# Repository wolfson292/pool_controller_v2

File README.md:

# pool_controller_v2
ESPHome Based Pool &amp; Spa Automation Controller

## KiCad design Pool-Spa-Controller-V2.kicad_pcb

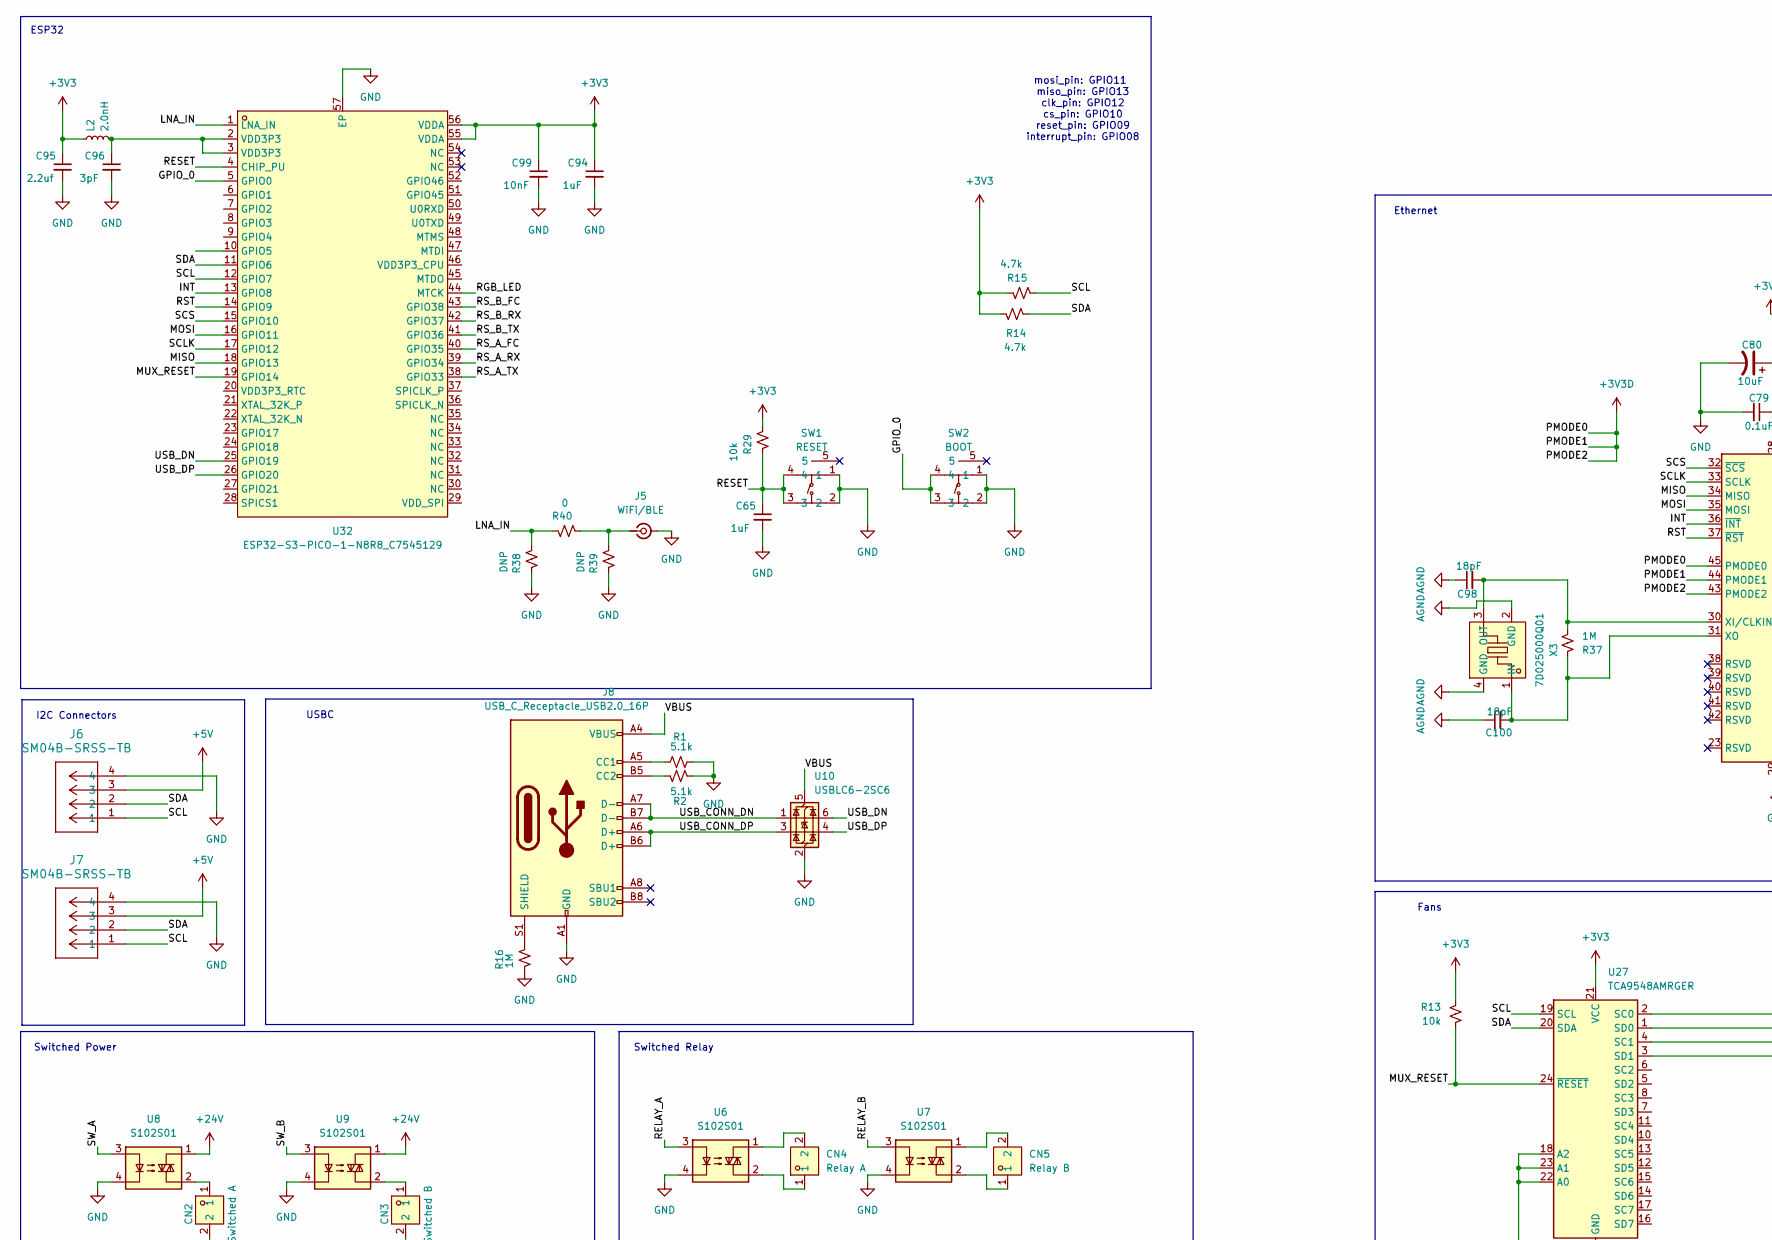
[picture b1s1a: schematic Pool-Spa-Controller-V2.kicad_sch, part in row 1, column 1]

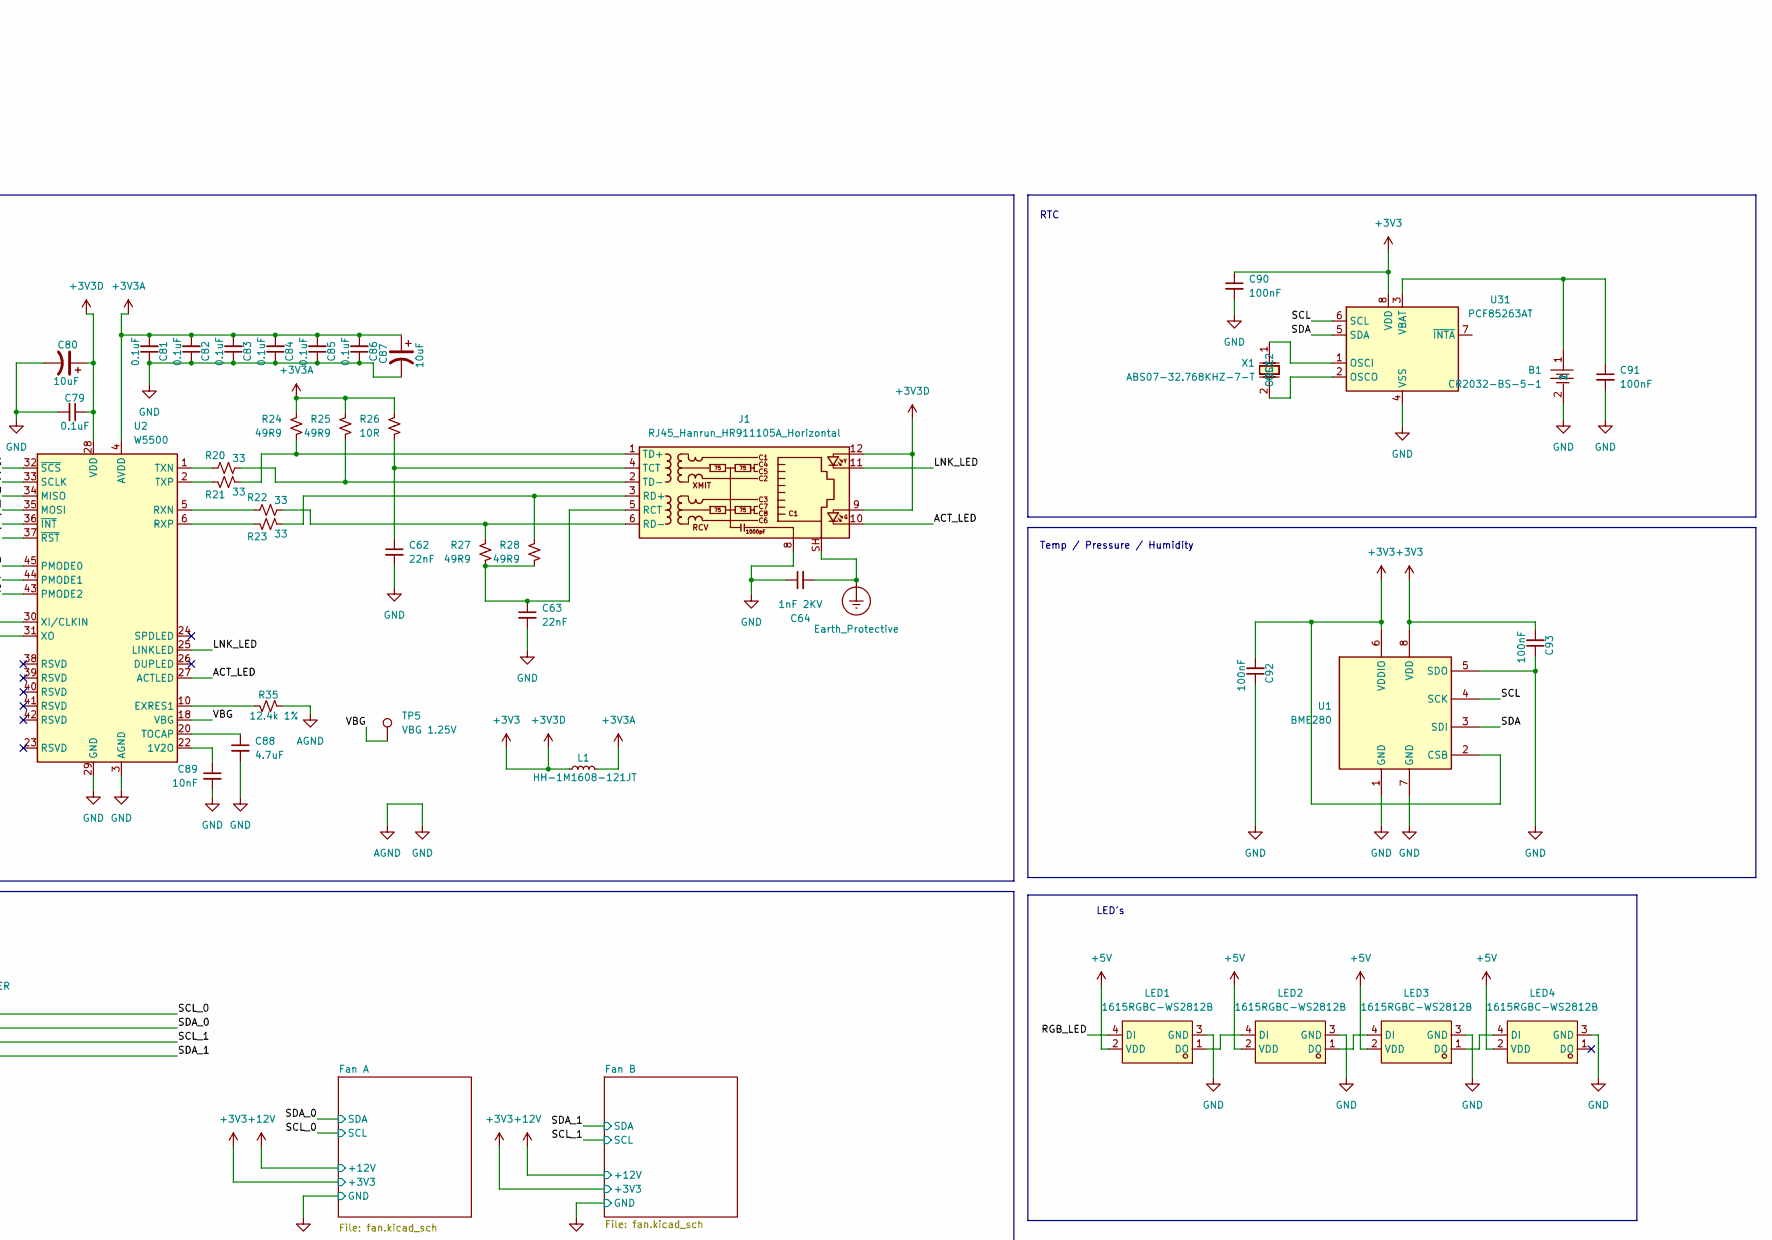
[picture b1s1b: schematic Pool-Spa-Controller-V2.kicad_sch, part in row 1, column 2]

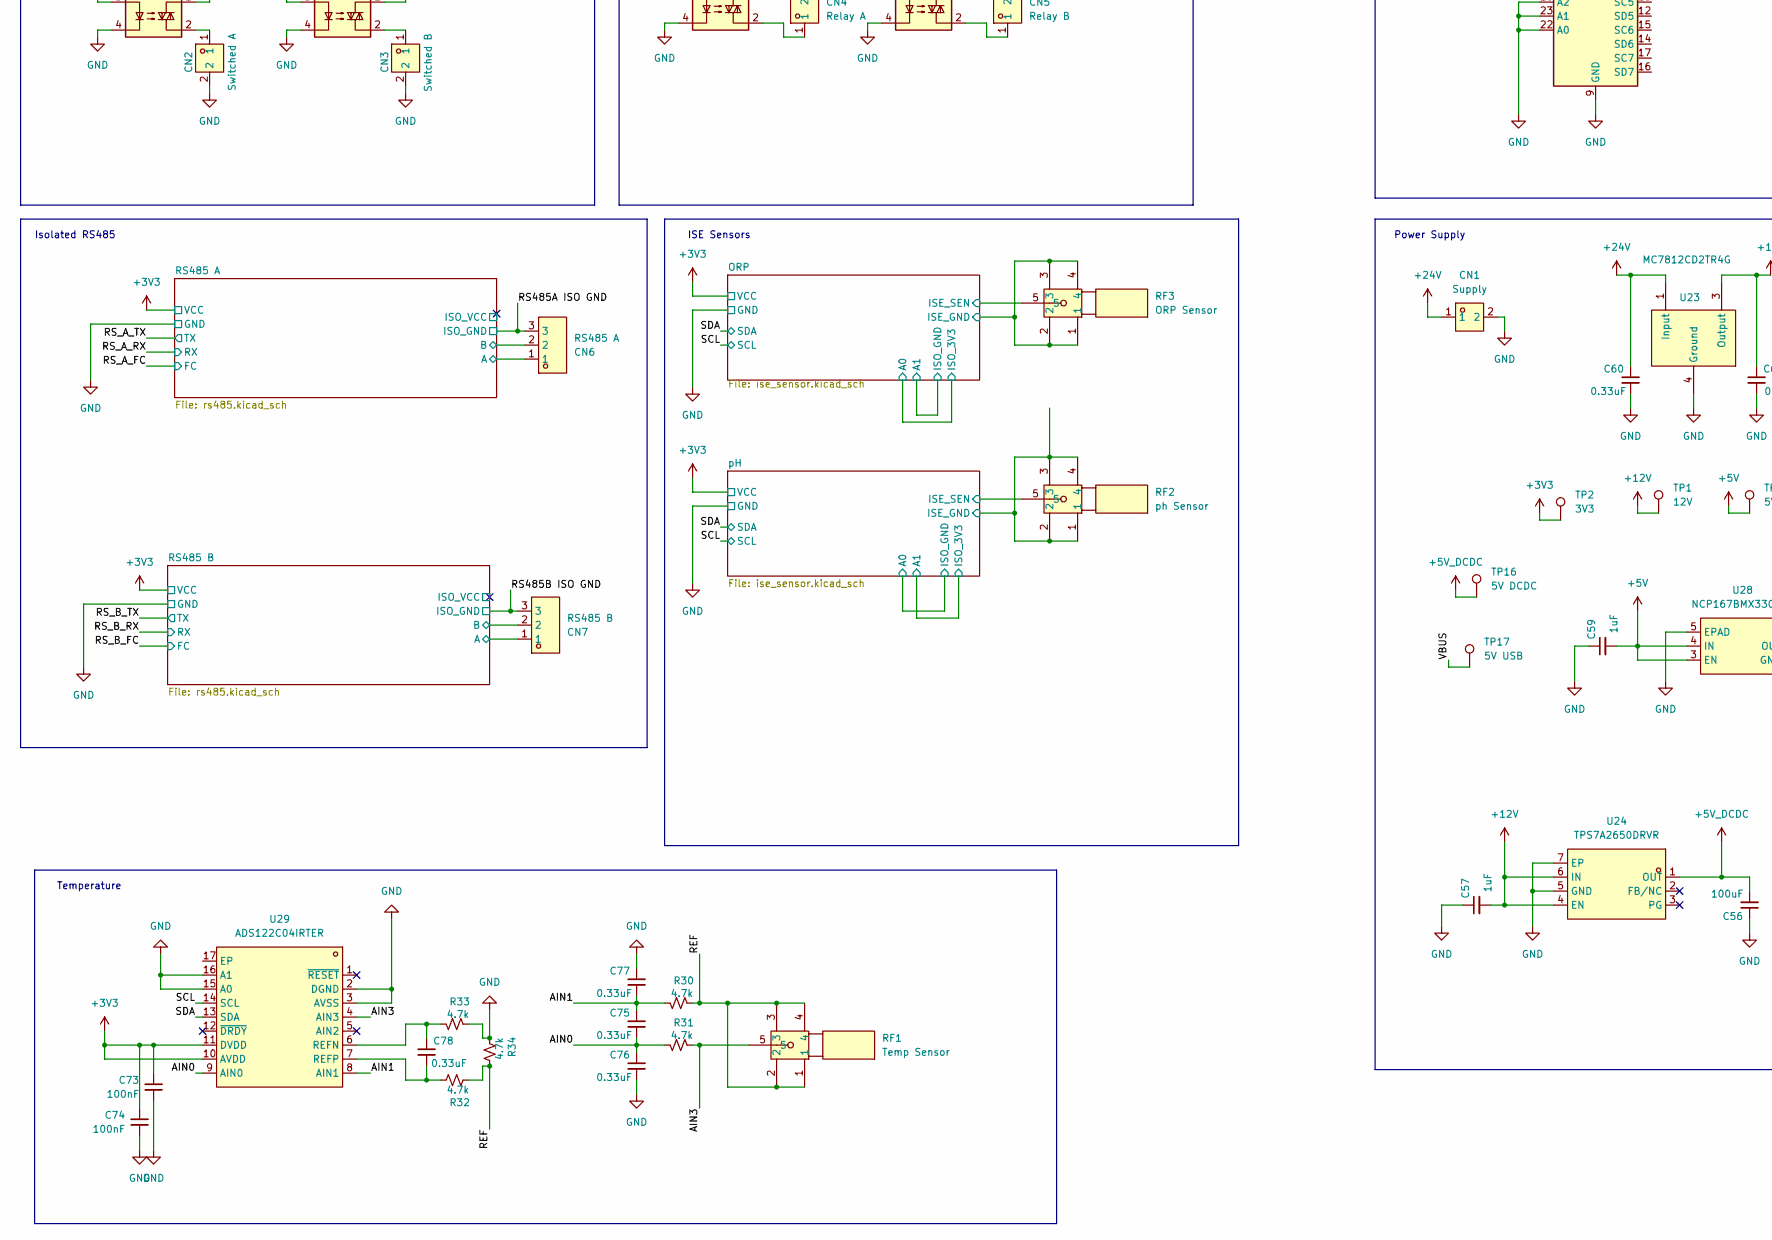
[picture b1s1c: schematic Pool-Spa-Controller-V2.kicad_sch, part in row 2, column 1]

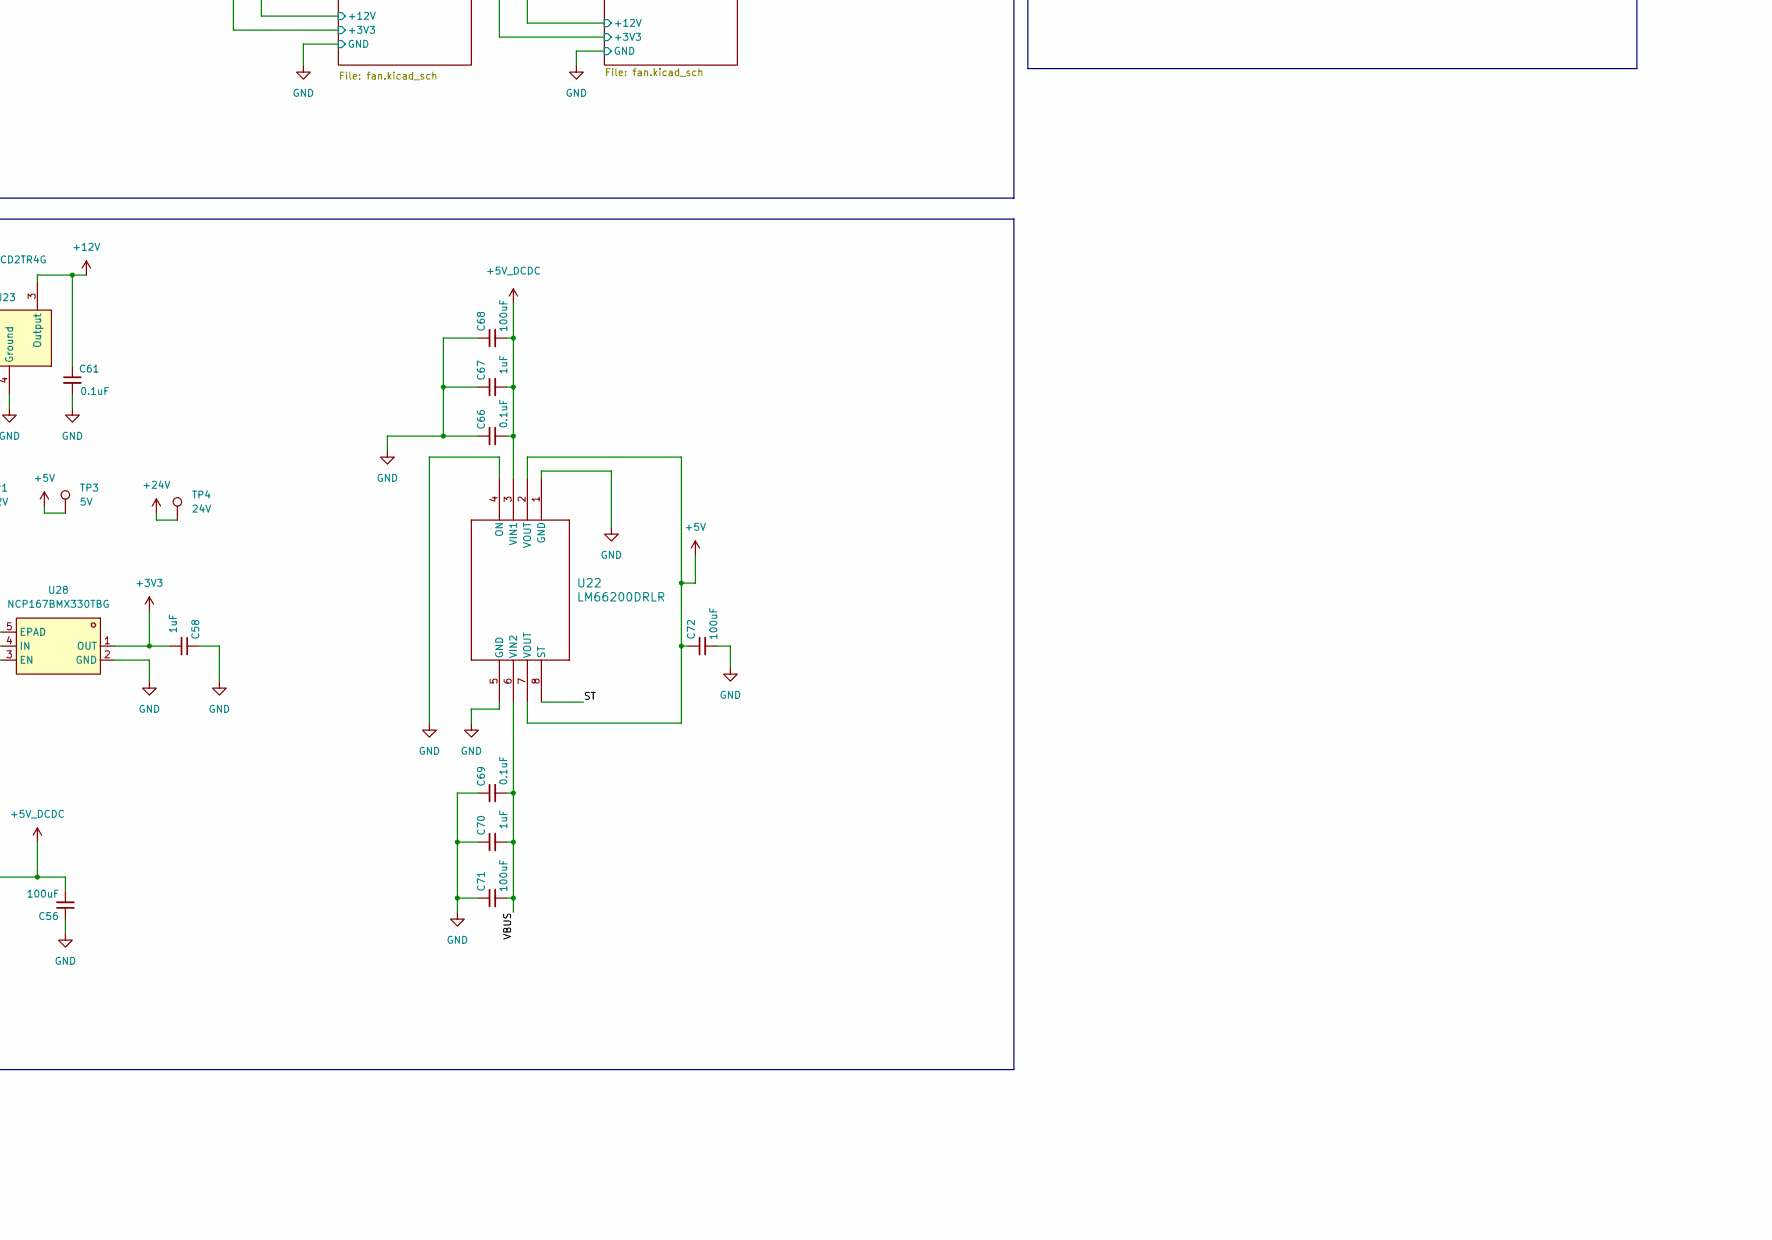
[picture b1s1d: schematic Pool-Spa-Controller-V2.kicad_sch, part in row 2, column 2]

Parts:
B1: CR2032-BS-5-1; BAT-TH_CR2032-BS-5-1; LCSC Part C70379
C56, C68, C71, C72: 100uF; C_0402_1005Metric
C57, C58, C59, C65, C67, C70, C94: 1uF; C_0402_1005Metric
C60, C75, C76, C77, C78: 0.33uF; C_0402_1005Metric
C61, C66, C69, C79, C81, C82, C83, C84, C85, C86: 0.1uF; C_0402_1005Metric
C62, C63: 22nF; C_0402_1005Metric
C64: 1nF 2KV; C_0402_1005Metric
C73, C74: 100nF; C_0402_1005Metric; MPN 100nF 0201
C80, C87: 10uF; CP_EIA-1608-08_AVX-J
C88: 4.7uF; C_0402_1005Metric
C89, C99: 10nF; C_0402_1005Metric
C90, C91, C92, C93: 100nF; C_0402_1005Metric
C95: 2.2uf; C_0402_1005Metric
C96: 3pF; C_0402_1005Metric
C98, C100: 18pF; C_0402_1005Metric
CN1: Supply; CONN-TH_2P-P2.54_1725656; LCSC Part C3029316
CN2: Switched A; CONN-TH_2P-P2.54_1725656; LCSC Part C3029316
CN3: Switched B; CONN-TH_2P-P2.54_1725656; LCSC Part C3029316
CN4: Relay A; CONN-TH_2P-P2.54_1725656; LCSC Part C3029316
CN5: Relay B; CONN-TH_2P-P2.54_1725656; LCSC Part C3029316
CN6: RS485 A; CONN-TH_3P-P2.54_1725669; LCSC Part C5288763
CN7: RS485 B; CONN-TH_3P-P2.54_1725669; LCSC Part C5288763
J1: RJ45_Hanrun_HR911105A_Horizontal
J5: WiFi/BLE; U.FL_Molex_MCRF_73412-0110_Vertical
J6, J7: SM04B-SRSS-TB; CONN_SM04B-SRSS-TB_JST
J8: USB_C_Receptacle_USB2.0_16P; USB_C_Receptacle_G-Switch_GT-USB-7010ASV
L1: HH-1M1608-121JT; L_0603_1608Metric
L2: 2.0nH; L_0402_1005Metric
LED1, LED2, LED3, LED4: 1615RGBC-WS2812B; LED-SMD_4P-L1.6-W1.5_XL-1615RGBC-WS2812B; LCSC Part C5349954
R1, R2: 5.1k; R_0402_1005Metric
R13: 10k; R_0402_1005Metric
R14, R15: 4.7k; R_0402_1005Metric; MPN 4.7k 0201
R16, R37: 1M; R_0402_1005Metric
R20, R21, R22, R23: 33; R_0402_1005Metric
R24, R25, R27, R28: 49R9; R_0402_1005Metric
R26: 10R; R_0402_1005Metric
R29: 10k; R_0402_1005Metric; MPN 4.7k 0201
R30, R31, R32, R33, R34: 4.7k; R_0402_1005Metric
R35: 12.4k 1%; R_0402_1005Metric
R38, R39: DNP; R_0402_1005Metric; MPN 4.7k 0201
R40: 0; R_0402_1005Metric; MPN 4.7k 0201
RF1: Temp Sensor; BNC-TH_DOSIN-801-0051; LCSC Part C521210
RF2: ph Sensor; BNC-TH_DOSIN-801-0051; LCSC Part C521210
RF3: ORP Sensor; BNC-TH_DOSIN-801-0051; LCSC Part C521210
SW1: RESET; SW-SMD_5P-L4.2-W2.8-P1.60-LS4.6-TR; LCSC Part C221678
SW2: BOOT; SW-SMD_5P-L4.2-W2.8-P1.60-LS4.6-TR; LCSC Part C221678
TP1: 12V; TestPoint_Pad_D1.0mm
TP2: 3V3; TestPoint_Pad_D1.0mm
TP3: 5V; TestPoint_Pad_D1.0mm
TP4: 24V; TestPoint_Pad_D1.0mm
TP5: VBG 1.25V; TestPoint_Pad_D1.0mm
TP16: 5V DCDC; TestPoint_Pad_D1.0mm
TP17: 5V USB; TestPoint_Pad_D1.0mm
U1: BME280; Bosch_LGA-8_2.5x2.5mm_P0.65mm_ClockwisePinNumbering
U2: W5500; LQFP-48_7x7mm_P0.5mm
U6, U7, U8, U9: S102S01; SIP4_Sharp-SSR_P7.62mm_Straight
U10: USBLC6-2SC6; SOT-23-6
U22: LM66200DRLR; SOT-5X3_DRL_TEX
U23: MC7812CD2TR4G; TO-263-2_L10.0-W9.1-P5.08-LS15.2-TL; LCSC Part C38744
U24: TPS7A2650DRVR; WSON-6_L2.0-W2.0-P0.65-TL-EP; LCSC Part C2866192
U27: TCA9548AMRGER; Texas_RGE0024C_VQFN-24-1EP_4x4mm_P0.5mm_EP2.1x2.1mm
U28: NCP167BMX330TBG; XDFN-4_L1.0-W1.0-P0.65-BL-EP; LCSC Part C892227
U29: ADS122C04IRTER; WQFN-16_L3.0-W3.0-P0.50-TL-EP0.8; LCSC Part C2670105
U31: PCF85263AT; SOIC-8_3.9x4.9mm_P1.27mm
U32: ESP32-S3-PICO-1-N8R8_C7545129; QFN-56_L7.0-W7.0-P0.40-TL-EP4.0; LCSC Part C7545129
X1: ABS07-32.768KHZ-7-T; OSC-SMD_L3.2-W1.5; LCSC Part C276424
X3: 7D025000Q01; CRYSTAL-SMD_4P-L2.0-W1.6-BL; LCSC Part C648942

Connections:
+3V3: C58.2, C73.1, C74.1, C79.1, C80.1, C90.1, C92.2, C93.2, C94.1, C95.1, C99.1, J1.9, J1.12, L1.1, L2.1, R13.1, R14.1, R15.2, R29.1, TP2.1, U1.2 (CSB), U1.6 (VDDIO), U1.8 (VDD), U2.28 (VDD), U2.43 (PMODE2), U2.44 (PMODE1), U2.45 (PMODE0), U27.21 (VCC), U28.1 (OUT), U29.10 (AVDD), U29.11 (DVDD), U31.8 (VDD), U32.55 (VDDA), U32.56 (VDDA); also elsewhere on the board
+3V3A: C81.2, C82.2, C83.2, C84.2, C85.2, C86.2, C87.1, L1.2, R24.1, R25.1, R26.1, U2.4 (AVDD), U2.8 (AVDD), U2.11 (AVDD), U2.15 (AVDD), U2.17 (AVDD), U2.21 (AVDD)
+5V: C59.2, C72.1, J6.3, J7.3, LED1.2 (VDD), LED2.2 (VDD), LED3.2 (VDD), LED4.2 (VDD), TP3.1, U22.2 (VOUT), U22.7 (VOUT), U28.3 (EN), U28.4 (IN)
+5V_DCDC: C56.2, C66.2, C67.2, C68.2, TP16.1, U22.3 (VIN1), U24.1 (OUT)
+12V: C57.2, C61.1, TP1.1, U23.3 (Output), U24.4 (EN), U24.6 (IN); also elsewhere on the board
+24V: C60.1, CN1.1, TP4.1, U8.1, U9.1, U23.1 (Input)
/ACT_LED: J1.10, U2.27 (ACTLED)
/AIN0: C75.2, C76.1, R31.2, U29.9 (AIN0)
/AIN1: C75.1, C77.2, R30.2, U29.8 (AIN1)
/AIN3: R31.1, RF1.5, U29.4 (AIN3)
/GPIO_0: SW2.3, SW2.4, U32.5 (GPIO0)
/INT: U2.36 (~INT), U32.13 (GPIO8)
/LNA_IN: R38.1, R40.2, U32.1 (LNA_IN)
/LNK_LED: J1.11, U2.25 (LINKLED)
/MISO: U2.34 (MISO), U32.18 (GPIO13)
/MOSI: U2.35 (MOSI), U32.16 (GPIO11)
/MUX_RESET: R13.2, U27.24 (~RESET), U32.19 (GPIO14)
/ORP/ISE_SEN: RF3.5; also elsewhere on the board
/ORP/ISO_GND: RF3.1, RF3.2, RF3.3, RF3.4; also elsewhere on the board
/REF: R30.1, R32.1, R34.2, RF1.1, RF1.2, RF1.3, RF1.4
/RELAY_A: U6.3
/RELAY_B: U7.3
/RESET: C65.1, R29.2, SW1.3, SW1.4, U32.4 (CHIP_PU)
/RGB_LED: LED1.4 (DI), U32.44 (MTCK)
/RS485 A/A: CN6.1; also elsewhere on the board
/RS485 A/B: CN6.2; also elsewhere on the board
/RS485 B/A: CN7.1; also elsewhere on the board
/RS485 B/B: CN7.2; also elsewhere on the board
/RS485A ISO GND: CN6.3; also elsewhere on the board
/RS485B ISO GND: CN7.3; also elsewhere on the board
/RST: U2.37 (~RST), U32.14 (GPIO9)
/RS_A_FC: U32.40 (GPIO35); also elsewhere on the board
/RS_A_RX: U32.39 (GPIO34); also elsewhere on the board
/RS_A_TX: U32.38 (GPIO33); also elsewhere on the board
/RS_B_FC: U32.43 (GPIO38); also elsewhere on the board
/RS_B_RX: U32.42 (GPIO37); also elsewhere on the board
/RS_B_TX: U32.41 (GPIO36); also elsewhere on the board
/SCL: J6.1, J7.1, R15.1, U1.4 (SCK), U27.19 (SCL), U29.14 (SCL), U31.6 (SCL), U32.12 (GPIO7); also elsewhere on the board
/SCLK: U2.33 (SCLK), U32.17 (GPIO12)
/SCL_0: U27.2 (SC0); also elsewhere on the board
/SCL_1: U27.4 (SC1); also elsewhere on the board
/SCS: U2.32 (~SCS), U32.15 (GPIO10)
/SDA: J6.2, J7.2, R14.2, U1.3 (SDI), U27.20 (SDA), U29.13 (SDA), U31.5 (SDA), U32.11 (GPIO6); also elsewhere on the board
/SDA_0: U27.1 (SD0); also elsewhere on the board
/SDA_1: U27.3 (SD1); also elsewhere on the board
/ST: U22.8 (ST)
/SW_A: U8.3
/SW_B: U9.3
/USB_CONN_DN: J8.A7 (D-), J8.B7 (D-), U10.1 (I/O1)
/USB_CONN_DP: J8.A6 (D+), J8.B6 (D+), U10.3 (I/O2)
/USB_DN: U10.6 (I/O1), U32.25 (GPIO19)
/USB_DP: U10.4 (I/O2), U32.26 (GPIO20)
/VBG: TP5.1, U2.18 (VBG)
/VBUS: C69.2, C70.2, C71.2, J8.A4 (VBUS), J8.A9 (VBUS), J8.B4 (VBUS), J8.B9 (VBUS), TP17.1, U10.5 (VBUS), U22.6 (VIN2)
/pH/ISE_SEN: RF2.5; also elsewhere on the board
/pH/ISO_GND: RF2.1, RF2.2, RF2.3, RF2.4; also elsewhere on the board
AGND: B1.2, C56.1, C57.1, C58.1, C59.1, C60.2, C61.2, C62.2, C63.2, C64.1, C65.2, C66.1, C67.1, C68.1, C69.1, C70.1, C71.1, C72.2, C73.2, C74.2, C76.2, C77.1, C79.2, C80.2, C81.1, C82.1, C83.1, C84.1, C85.1, C86.1, C87.2, C88.2, C89.2, C90.2, C91.2, C92.1, C93.1, C94.2, C95.2, C96.2, C98.1, C99.2, C100.1, CN1.2, CN2.2, CN3.2, J1.8, J5.2 (Ext), J6.4, J7.4, J8.A1 (GND), J8.A12 (GND), J8.B1 (GND), J8.B12 (GND), LED1.3 (GND), LED2.3 (GND), LED3.3 (GND), LED4.3 (GND), R1.2, R2.2, R16.2, R33.1, R34.1, R35.2, R38.2, R39.2, SW1.1, SW1.2, SW2.1, SW2.2, U1.1 (GND), U1.5 (SDO), U1.7 (GND), U2.3 (AGND), U2.9 (AGND), U2.14 (AGND), U2.16 (AGND), U2.19 (AGND), U2.29 (GND), U2.48 (AGND), U6.4, U7.4, U8.4, U9.4, U10.2 (GND), U22.1 (GND), U22.4 (ON), U22.5 (GND), U23.4 (Ground), U24.5 (GND), U24.7 (EP), U27.9 (GND), U27.18 (A2), U27.22 (A0), U27.23 (A1), U28.2 (GND), U28.5 (EPAD), U29.2 (DGND), U29.3 (AVSS), U29.15 (A0), U29.16 (A1), U31.4 (VSS), U32.57 (EP), X3.2 (GND), X3.4 (GND); also elsewhere on the board
Earth_Protective: C64.2, J1.SH
unnamed: C96.1, L2.2, U32.2 (VDD3P3), U32.3 (VDD3P3)
unnamed: CN2.1, U8.2
unnamed: CN3.1, U9.2
unnamed: CN4.1, U6.2
unnamed: CN4.2, U6.1
unnamed: CN5.1, U7.2
unnamed: CN5.2, U7.1
unnamed: C63.1, J1.5 (RCT), R27.2, R28.2
unnamed: J1.3 (RD+), R23.2, R28.1
unnamed: J1.6 (RD-), R22.2, R27.1
unnamed: C62.1, J1.4 (TCT), R26.2
unnamed: J1.1 (TD+), R21.2, R24.2
unnamed: J1.2 (TD-), R20.2, R25.2
unnamed: J5.1 (In), R39.1, R40.1
unnamed: J8.A5 (CC1), R1.1
unnamed: J8.B5 (CC2), R2.1
unnamed: J8.S1 (SHIELD), R16.1
unnamed: LED1.1 (DO), LED2.4 (DI)
unnamed: LED2.1 (DO), LED3.4 (DI)
unnamed: LED3.1 (DO), LED4.4 (DI)
unnamed: C89.1, U2.22 (1V2O)
unnamed: R35.1, U2.10 (EXRES1)
unnamed: R22.1, U2.5 (RXN)
unnamed: R23.1, U2.6 (RXP)
unnamed: C88.1, U2.20 (TOCAP)
unnamed: R20.1, U2.1 (TXN)
unnamed: R21.1, U2.2 (TXP)
unnamed: C98.2, R37.2, U2.30 (XI/CLKIN), X3.3 (OUT)
unnamed: C100.2, R37.1, U2.31 (XO), X3.1 (IN)
unnamed: C78.1, R33.2, U29.6 (REFN)
unnamed: C78.2, R32.2, U29.7 (REFP)
unnamed: U31.1 (OSCI), X1.1 (OSC1)
unnamed: U31.2 (OSCO), X1.2 (OSC2)
unnamed: B1.1, C91.1, U31.3 (VBAT)

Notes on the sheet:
Switched Power
Switched Relay
ISE Sensors
Temperature
mosi_pin: GPIO11 miso_pin: GPIO13 clk_pin: GPIO12 cs_pin: GPIO10 reset_pin: GPIO09 interrupt_pin: GPIO08
I2C Connectors
LED's
USBC
Ethernet
Power Supply
RTC
ESP32
Temp / Pressure / Humidity
Isolated RS485
Fans

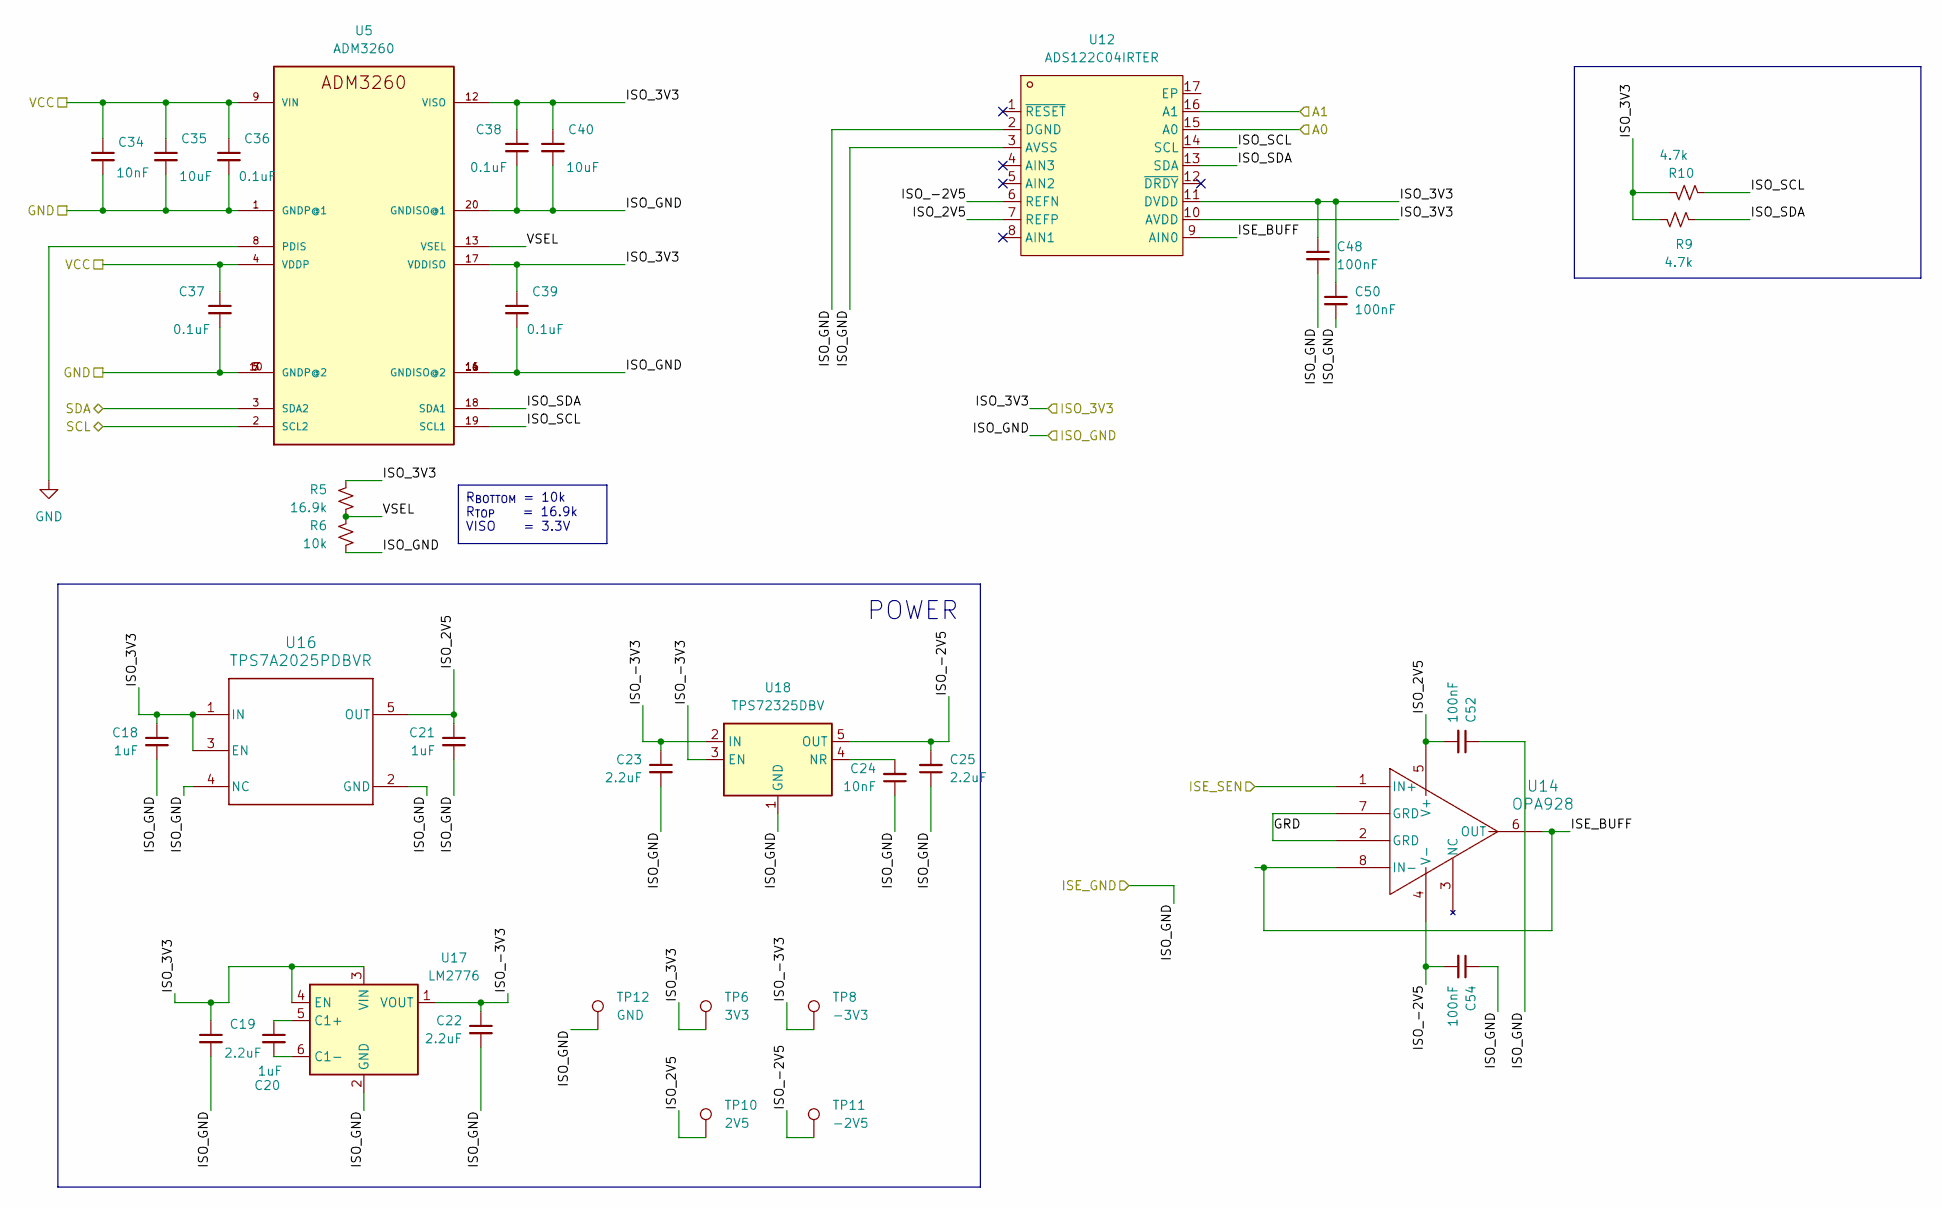
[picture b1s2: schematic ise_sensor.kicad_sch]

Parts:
C18, C20, C21: 1uF; C_0402_1005Metric; MPN 1uF 0201
C19, C22: 2.2uF; C_0402_1005Metric; MPN 1uF 0201
C23, C25: 2.2uF; C_0402_1005Metric; MPN 2.2uF 0201
C24, C34: 10nF; C_0402_1005Metric; MPN 10nF 0201
C35, C40: 10uF; C_0402_1005Metric; MPN 10uF 0201
C36, C37, C38, C39: 0.1uF; C_0402_1005Metric; MPN 0.1uF 0201
C48, C50: 100nF; C_0402_1005Metric; MPN 100nF 0201
C52, C54: 100nF; C_0402_1005Metric
R5: 16.9k; R_0402_1005Metric; MPN 30.9k 0201
R6: 10k; R_0402_1005Metric; MPN 10k 0201
R9, R10: 4.7k; R_0402_1005Metric; MPN 4.7k 0201
TP6: 3V3; TestPoint_Pad_D1.0mm
TP8: -3V3; TestPoint_Pad_D1.0mm
TP10: 2V5; TestPoint_Pad_D1.0mm
TP11: -2V5; TestPoint_Pad_D1.0mm
TP12: GND; TestPoint_Pad_D1.0mm
U5: ADM3260; ADM3260_SOP65P780X200-20N
U12: ADS122C04IRTER; WQFN-16_L3.0-W3.0-P0.50-TL-EP0.8; LCSC Part C2670105
U14: OPA928; SOIC8_D_TEX
U16: TPS7A2025PDBVR; DBV0005A-IPC_A
U17: LM2776; SOT-23-6
U18: TPS72325DBV; SOT-23-5

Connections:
+3V3: C34.1, C35.1, C36.1, C37.1, U5.4 (VDDP), U5.9 (VIN); also elsewhere on the board
/ORP/GRD: U14.2 (GRD), U14.7 (GRD)
/ORP/ISE_BUFF: U12.9 (AIN0), U14.6 (OUT), U14.8 (IN-)
/ORP/ISE_SEN: U14.1 (IN+); also elsewhere on the board
/ORP/ISO_2V5: C21.1, C52.2, TP10.1, U12.7 (REFP), U14.5 (V+), U16.5 (OUT)
/ORP/ISO_3V3: C18.1, C19.1, C38.1, C39.1, C40.1, C48.1, C50.1, R5.2, R9.1, R10.2, TP6.1, U5.12 (VISO), U5.17 (VDDISO), U12.10 (AVDD), U12.11 (DVDD), U12.15 (A0), U16.1 (IN), U16.3 (EN), U17.3 (VIN), U17.4 (EN)
/ORP/ISO_-2V5: C25.2, C54.2, TP11.1, U12.6 (REFN), U14.4 (V-), U18.5 (OUT)
/ORP/ISO_-3V3: C22.1, C23.1, TP8.1, U17.1 (VOUT), U18.2 (IN), U18.3 (EN)
/ORP/ISO_GND: C18.2, C19.2, C21.2, C22.2, C23.2, C24.1, C25.1, C38.2, C39.2, C40.2, C48.2, C50.2, C52.1, C54.1, R6.2, TP12.1, U5.11 (GNDISO@2), U5.14 (GNDISO@2), U5.16 (GNDISO@2), U5.20 (GNDISO@1), U12.2 (DGND), U12.3 (AVSS), U12.16 (A1), U16.2 (GND), U16.4 (NC), U17.2 (GND), U18.1 (GND); also elsewhere on the board
/ORP/ISO_SCL: R10.1, U5.19 (SCL1), U12.14 (SCL)
/ORP/ISO_SDA: R9.2, U5.18 (SDA1), U12.13 (SDA)
/ORP/VSEL: R5.1, R6.1, U5.13 (VSEL)
/SCL: U5.2 (SCL2); also elsewhere on the board
/SDA: U5.3 (SDA2); also elsewhere on the board
AGND: C34.2, C35.2, C36.2, C37.2, U5.1 (GNDP@1), U5.5 (GNDP@2), U5.7 (GNDP@2), U5.8 (PDIS), U5.10 (GNDP@2); also elsewhere on the board
unnamed: C20.1, U17.5 (C1+)
unnamed: C20.2, U17.6 (C1-)
unnamed: C24.2, U18.4 (NR)

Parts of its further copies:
C26, C28, C29: 1uF; C_0402_1005Metric; MPN 1uF 0201
C27, C30: 2.2uF; C_0402_1005Metric; MPN 1uF 0201
C31, C33: 2.2uF; C_0402_1005Metric; MPN 2.2uF 0201
C32, C41: 10nF; C_0402_1005Metric; MPN 10nF 0201
C42, C47: 10uF; C_0402_1005Metric; MPN 10uF 0201
C43, C44, C45, C46: 0.1uF; C_0402_1005Metric; MPN 0.1uF 0201
C49, C51: 100nF; C_0402_1005Metric; MPN 100nF 0201
C53, C55: 100nF; C_0402_1005Metric
R7: 16.9k; R_0402_1005Metric; MPN 30.9k 0201
R8: 10k; R_0402_1005Metric; MPN 10k 0201
R11, R12: 4.7k; R_0402_1005Metric; MPN 4.7k 0201
TP7: 3V3; TestPoint_Pad_D1.0mm
TP9: -3V3; TestPoint_Pad_D1.0mm
TP13: GND; TestPoint_Pad_D1.0mm
TP14: 2V5; TestPoint_Pad_D1.0mm
TP15: -2V5; TestPoint_Pad_D1.0mm
U11: ADM3260; ADM3260_SOP65P780X200-20N
U13: ADS122C04IRTER; WQFN-16_L3.0-W3.0-P0.50-TL-EP0.8; LCSC Part C2670105
U15: OPA928; SOIC8_D_TEX
U19: TPS7A2025PDBVR; DBV0005A-IPC_A
U20: LM2776; SOT-23-6
U21: TPS72325DBV; SOT-23-5

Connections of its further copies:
+3V3: C41.1, C42.1, C43.1, C44.1, U11.4 (VDDP), U11.9 (VIN); also elsewhere on the board
/SCL: U11.2 (SCL2); also elsewhere on the board
/SDA: U11.3 (SDA2); also elsewhere on the board
/pH/GRD: U15.2 (GRD), U15.7 (GRD)
/pH/ISE_BUFF: U13.9 (AIN0), U15.6 (OUT), U15.8 (IN-)
/pH/ISE_SEN: U15.1 (IN+); also elsewhere on the board
/pH/ISO_2V5: C29.1, C53.2, TP14.1, U13.7 (REFP), U15.5 (V+), U19.5 (OUT)
/pH/ISO_3V3: C26.1, C27.1, C45.1, C46.1, C47.1, C49.1, C51.1, R7.2, R11.1, R12.2, TP7.1, U11.12 (VISO), U11.17 (VDDISO), U13.10 (AVDD), U13.11 (DVDD), U13.16 (A1), U19.1 (IN), U19.3 (EN), U20.3 (VIN), U20.4 (EN)
/pH/ISO_-2V5: C33.2, C55.2, TP15.1, U13.6 (REFN), U15.4 (V-), U21.5 (OUT)
/pH/ISO_-3V3: C30.1, C31.1, TP9.1, U20.1 (VOUT), U21.2 (IN), U21.3 (EN)
/pH/ISO_GND: C26.2, C27.2, C29.2, C30.2, C31.2, C32.1, C33.1, C45.2, C46.2, C47.2, C49.2, C51.2, C53.1, C55.1, R8.2, TP13.1, U11.11 (GNDISO@2), U11.14 (GNDISO@2), U11.16 (GNDISO@2), U11.20 (GNDISO@1), U13.2 (DGND), U13.3 (AVSS), U13.15 (A0), U19.2 (GND), U19.4 (NC), U20.2 (GND), U21.1 (GND); also elsewhere on the board
/pH/ISO_SCL: R12.1, U11.19 (SCL1), U13.14 (SCL)
/pH/ISO_SDA: R11.2, U11.18 (SDA1), U13.13 (SDA)
/pH/VSEL: R7.1, R8.1, U11.13 (VSEL)
AGND: C41.2, C42.2, C43.2, C44.2, U11.1 (GNDP@1), U11.5 (GNDP@2), U11.7 (GNDP@2), U11.8 (PDIS), U11.10 (GNDP@2); also elsewhere on the board
unnamed: C28.1, U20.5 (C1+)
unnamed: C28.2, U20.6 (C1-)
unnamed: C32.2, U21.4 (NR)

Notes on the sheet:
POWER
R_{BOTTOM} = 10k R_{TOP} = 16.9k VISO = 3.3V

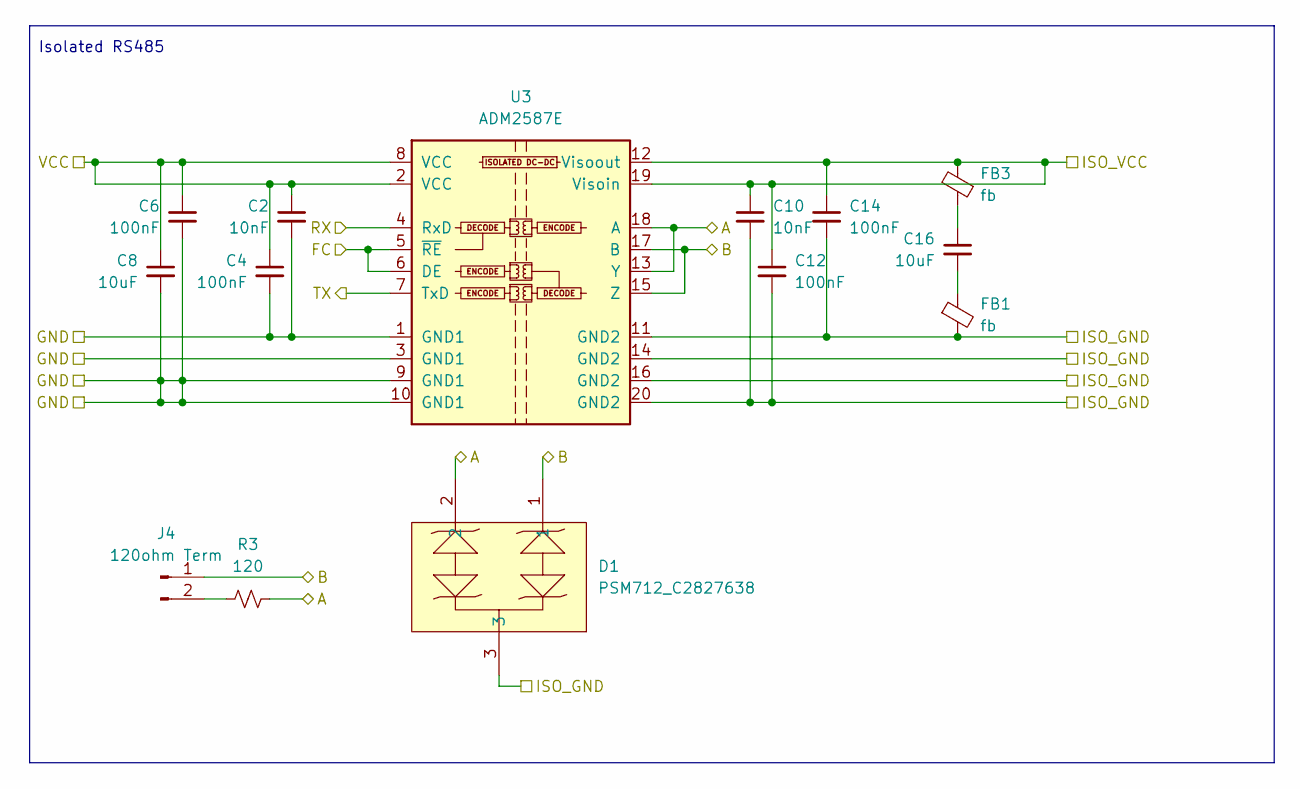
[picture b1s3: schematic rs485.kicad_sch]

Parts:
C2, C10: 10nF; C_0402_1005Metric
C4, C6, C12, C14: 100nF; C_0402_1005Metric
C8, C16: 10uF; C_0402_1005Metric
D1: PSM712_C2827638; SOT-23-3_L2.9-W1.3-P1.90-LS2.4-BL-2; LCSC Part C2827638
FB1, FB3: fb; L_0402_1005Metric
J4: 120ohm Term; PinHeader_1x02_P2.54mm_Vertical
R3: 120; R_0402_1005Metric
U3: ADM2587E; SOIC-20W_7.5x12.8mm_P1.27mm

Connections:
+3V3: C2.1, C4.1, C6.1, C8.1, U3.2 (VCC), U3.8 (VCC); also elsewhere on the board
/RS485 A/A: D1.2, R3.2, U3.13 (Y), U3.18 (A); also elsewhere on the board
/RS485 A/B: D1.1, J4.1, U3.15 (Z), U3.17 (B); also elsewhere on the board
/RS485 A/ISO_VCC: C10.1, C12.1, C14.1, FB3.2, U3.12 (Visoout), U3.19 (Visoin)
/RS485A ISO GND: C10.2, C12.2, C14.2, D1.3, FB1.2, U3.11 (GND2), U3.14 (GND2), U3.16 (GND2), U3.20 (GND2); also elsewhere on the board
/RS_A_FC: U3.5 (~RE), U3.6 (DE); also elsewhere on the board
/RS_A_RX: U3.4 (RxD); also elsewhere on the board
/RS_A_TX: U3.7 (TxD); also elsewhere on the board
AGND: C2.2, C4.2, C6.2, C8.2, U3.1 (GND1), U3.3 (GND1), U3.9 (GND1), U3.10 (GND1); also elsewhere on the board
unnamed: C16.1, FB3.1
unnamed: C16.2, FB1.1
unnamed: J4.2, R3.1

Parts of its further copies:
C3, C11: 10nF; C_0402_1005Metric
C5, C7, C13, C15: 100nF; C_0402_1005Metric
C9, C17: 10uF; C_0402_1005Metric
D2: PSM712_C2827638; SOT-23-3_L2.9-W1.3-P1.90-LS2.4-BL-2; LCSC Part C2827638
FB2, FB4: fb; L_0402_1005Metric
J9: 120ohm Term; PinHeader_1x02_P2.54mm_Vertical
R4: 120; R_0402_1005Metric
U4: ADM2587E; SOIC-20W_7.5x12.8mm_P1.27mm

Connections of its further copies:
+3V3: C3.1, C5.1, C7.1, C9.1, U4.2 (VCC), U4.8 (VCC); also elsewhere on the board
/RS485 B/A: D2.2, R4.2, U4.13 (Y), U4.18 (A); also elsewhere on the board
/RS485 B/B: D2.1, J9.1, U4.15 (Z), U4.17 (B); also elsewhere on the board
/RS485 B/ISO_VCC: C11.1, C13.1, C15.1, FB4.2, U4.12 (Visoout), U4.19 (Visoin)
/RS485B ISO GND: C11.2, C13.2, C15.2, D2.3, FB2.2, U4.11 (GND2), U4.14 (GND2), U4.16 (GND2), U4.20 (GND2); also elsewhere on the board
/RS_B_FC: U4.5 (~RE), U4.6 (DE); also elsewhere on the board
/RS_B_RX: U4.4 (RxD); also elsewhere on the board
/RS_B_TX: U4.7 (TxD); also elsewhere on the board
AGND: C3.2, C5.2, C7.2, C9.2, U4.1 (GND1), U4.3 (GND1), U4.9 (GND1), U4.10 (GND1); also elsewhere on the board
unnamed: C17.1, FB4.1
unnamed: C17.2, FB2.1
unnamed: J9.2, R4.1

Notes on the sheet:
Isolated RS485
